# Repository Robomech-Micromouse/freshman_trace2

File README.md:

# freshman_trace2

1,DRCをチェックしておらず、GNDが分離していたので修正しました。

2,フォトリフレクタの配置を裏表逆にしていたので修正しました。

3,羽部分の6ピンを2.00mmピッチにしていたので2.54mmピッチに修正しました。

4,そのほか、外周をGNDで囲んだり、アンテナになっていそうなGNDを極力減らしました。

100mm×100mmに収めているのでJLCPCBで頼むと一週間ぐらいかかる代わりに送料が100円です。ﾔｽｩｲ

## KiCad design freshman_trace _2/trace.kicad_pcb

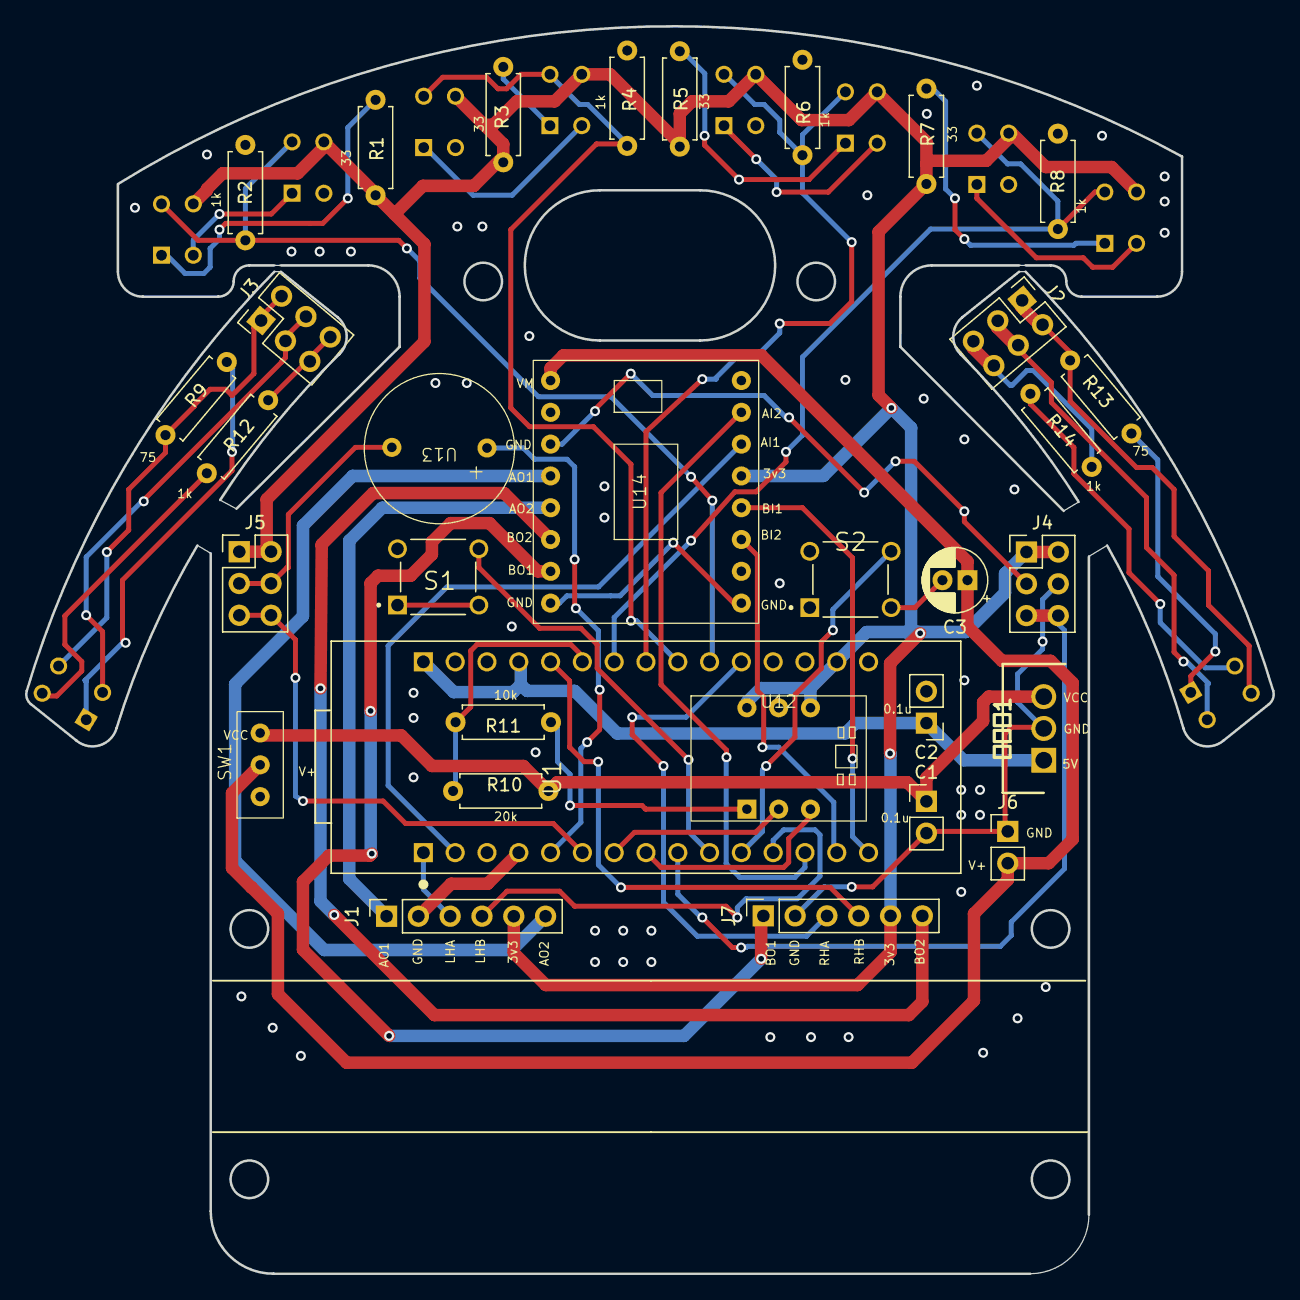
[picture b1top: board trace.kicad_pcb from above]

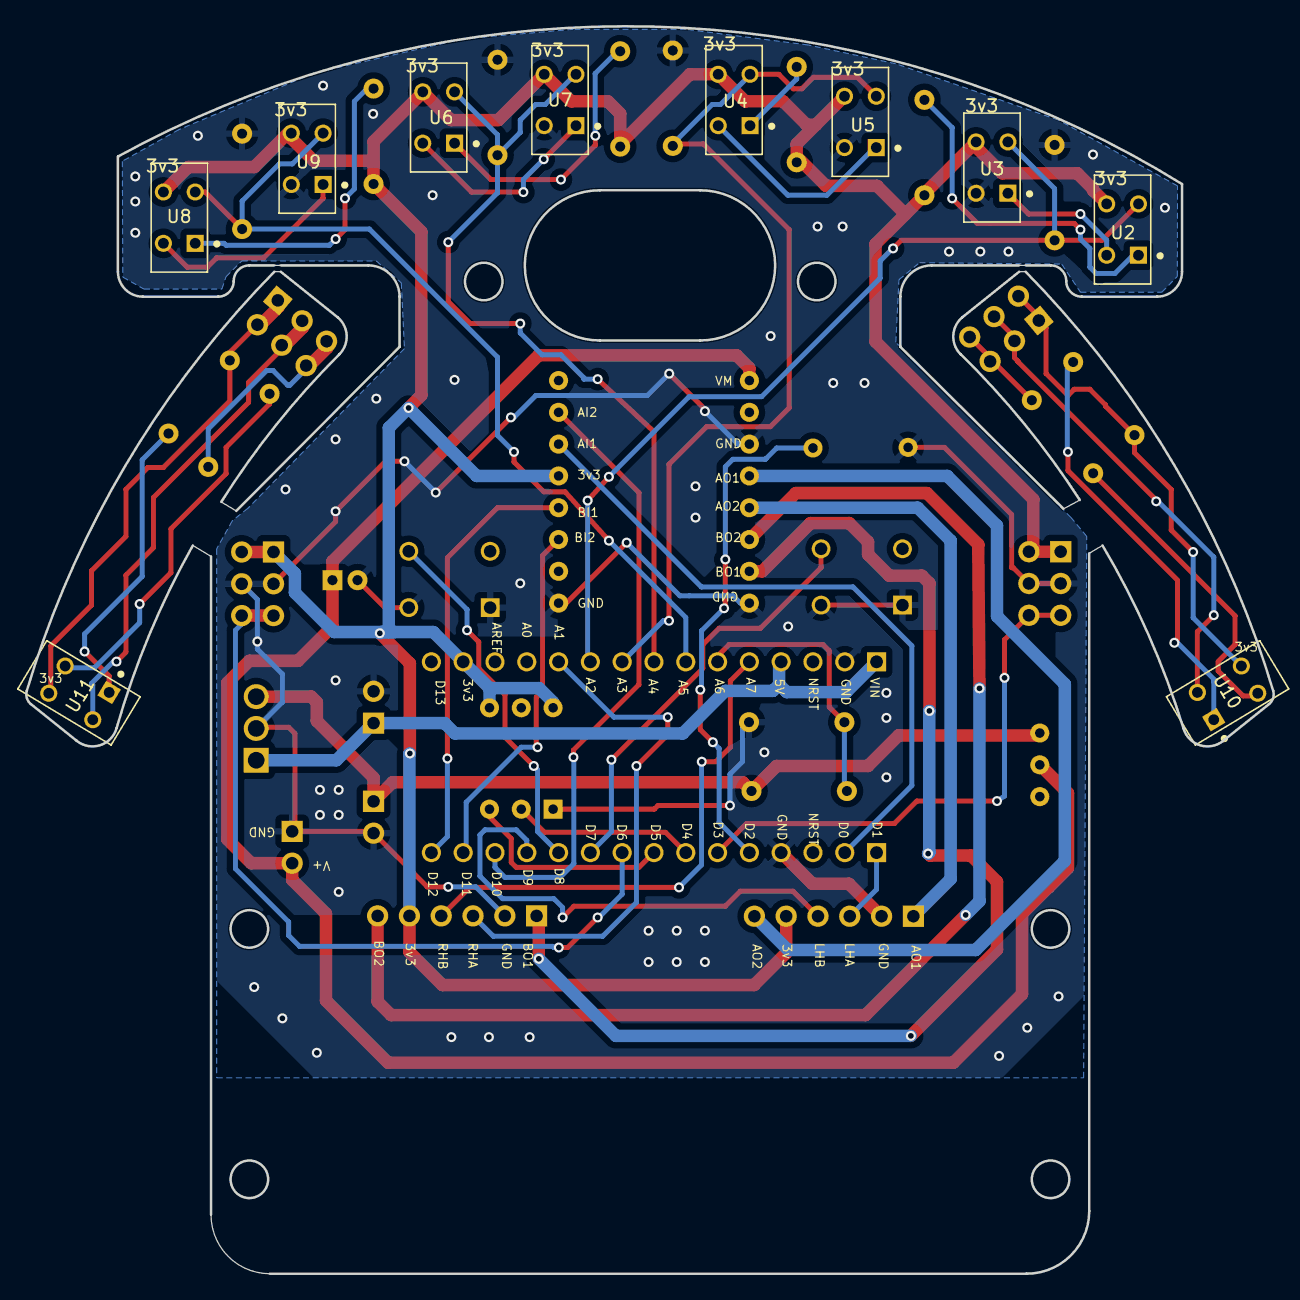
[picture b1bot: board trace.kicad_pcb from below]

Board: 4 copper layers, 99.6 x 99.6 mm, 42 parts (10 on the bottom side), 47 nets.

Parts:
C1, C2: 0.1u; PinHeader_1x02_P2.54mm_Vertical
C3: C_Polarized; CP_Radial_D5.0mm_P2.00mm
J1: L; PinSocket_1x06_P2.54mm_Vertical
J2, J3, J4, J5: Conn_02x03_Counter_Clockwise; PinHeader_2x03_P2.54mm_Vertical
J6: Conn_01x02_Socket; PinHeader_1x02_P2.54mm_Vertical
J7: R; PinSocket_1x06_P2.54mm_Vertical
R1, R3, R5, R7: 33 1%; R_Axial_DIN0207_L6.3mm_D2.5mm_P7.62mm_Horizontal
R2, R4, R6, R8, R12, R14: 1k; R_Axial_DIN0207_L6.3mm_D2.5mm_P7.62mm_Horizontal
R9, R13: 75 1%; R_Axial_DIN0207_L6.3mm_D2.5mm_P7.62mm_Horizontal
R10: 20k; R_Axial_DIN0207_L6.3mm_D2.5mm_P7.62mm_Horizontal
R11: 10k; R_Axial_DIN0207_L6.3mm_D2.5mm_P7.62mm_Horizontal
S1, S2: TL1105AF160Q; SW_TL1105AF160Q
SW1: SW_SPDT; SS-12D00G3
U1: NUCLEO-F303K8; MODULE_NUCLEO-F303K8
U2, U3, U4, U5, U6, U7, U8, U9, U10, U11: LTH-1550-01; PHOTOINTERRUPTER_LTH-1550-01
U12: BMX055
U13: buzaa
U14: drv8833
三端子1: Conn_01x03_Pin; NJM7805FA

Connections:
+3.3V: J1.5, J4.1, J4.2, J5.1, J5.2, J7.5, R1.1, R3.1, R5.1, R7.1, U1.4_14 (+3V3), U2.3, U3.3, U4.3, U5.3, U6.3, U7.3, U8.3, U9.3, U12.1 (VCC), U12.3 (3v3), U14.12 (STBY)
+5V: C2.1, U1.4_1 (VIN), U1.4_4 (+5V), 三端子1.1
AIN1: U1.3_2 (PA10), U14.11 (AIN1)
AIN2: U1.3_13 (PA11), U14.10 (AIN2)
BIN1: U1.3_15 (PB4), U14.13 (BIN1)
BIN2: U1.3_14 (PB5), U14.14 (BIN2)
BSEN: R10.2, R11.1, U1.4_6 (PA7)
FLS: R4.1, U1.4_9 (PA4), U4.2, U5.2
FRS: R6.1, U1.4_8 (PA5), U6.2, U7.2
GND: C1.2, C2.2, C3.2, J1.2, J4.3, J4.4, J5.3, J5.4, J6.1, J7.2, R2.2, R4.2, R6.2, R8.2, R11.2, S1.1, S1.2, S2.1, S2.2, U1.3_4 (GND_1), U1.4_2 (GND_2), U3.4, U5.4, U7.4, U9.4, U12.4 (GND), U13.2 (OUT), U14.1 (GND), U14.6 (GND), U14.16 (GND), 三端子1.2
LHallA: J1.3, U1.3_1 (PA9)
LHallB: J1.4, U1.3_12 (PA8)
LLS: R2.1, U1.4_10 (PA3), U2.2, U3.2
MLS: J4.5, J4.6, U1.3_9 (PB1)
MRS: J5.5, J5.6, U1.3_6 (PB0)
unnamed: J1.1, U14.4 (AO2)
unnamed: J1.6, U14.5 (AO1)
unnamed: J2.1, J2.2, R13.1, U11.3
unnamed: J2.3, J2.4, U11.4
unnamed: J2.5, J2.6, R14.2
unnamed: J3.1, J3.2, R9.1, U10.3
unnamed: J3.3, J3.4, U10.4
unnamed: J3.5, J3.6, R12.2
unnamed: J7.1, U14.2 (BO1)
unnamed: J7.6, U14.3 (BO2)
unnamed: R1.2, U2.1
unnamed: R3.2, U4.1
unnamed: R5.2, U6.1
unnamed: R7.2, U8.1
unnamed: R9.2, U10.1
unnamed: R12.1, U10.2
unnamed: R13.2, U11.1
unnamed: R14.1, U11.2
unnamed: S1.4, U1.3_10 (PF0)
unnamed: S2.4, U1.3_11 (PF1)
unnamed: U2.4, U3.1
unnamed: U4.4, U5.1
unnamed: U6.4, U7.1
unnamed: U8.4, U9.1
unnamed: U1.3_5 (PA12), U13.1 (IN)
RHallA: J7.3, U1.4_11 (PA1)
RHallB: J7.4, U1.4_5 (PA2)
RRS: R8.1, U1.4_7 (PA6), U8.2, U9.2
SCL: U1.3_8 (PB6), U12.6 (SCL)
SDA: U1.3_7 (PB7), U12.5 (SDA)
VCC: C1.1, R10.1, SW1.1 (A), 三端子1.3
VDD: C3.1, J6.2, SW1.2 (B), U14.8 (VM)
